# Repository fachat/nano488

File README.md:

# nano488

An IEEE488 interface for the PC using USB and an Arduino Nano (tm)

## Design

This IEEE488 interfaces uses an Arduino Nano (tm) and its serial-over-USB interface to have a PC control the IEEE488 interface.

The design is made to be able to work as both, a controller or a device, but the main purpose is to work as
a disk drive for the Commodore PET computers.

The design is inspired by https://github.com/Twilight-Logic/AR488 but I had to rearrange some lines to
add the Commodore disk drive's ATNA response circuit.

Also, the design uses the standards compliant 75160/75161 IEEE488 drivers, so electrical specifications are met.

Note, that no extra power supply line e.g. to the tape port is required, as the board is using the 5V
supplied by the USB bus connector (via the Arduino nano (tm))

## Software

The software that supports the disk drive functionality is XD2031 ( https://github.com/fachat/XD2031 ) - for details see there.

## Boards

### V1.1B

This board has four IEEE488 connectors:

1. a board edge connector similar to the Commodore PET IEEE488 connector
2. a slot connector to plug the device directly onto the Commodore PET IEEE488 connector
3. a 24 pin standards IEEE488 connector for standard IEEE488 stacking cables
4. a 24 pin flat ribbon connector

Here are the design files:

- [Eagle schematics](v1.1b/nano_ieee488_v1.1b.sch)
- [Eagle layout](v1.1b/nano_ieee488_v1.1b.brd)
- [Schematics picture](v1.1b/nano_ieee488_v1.1b-sch.png)
- [Board parts layout](v1.1b/nano_ieee488_v1.1b-layout.png)
- [Board full layout](v1.1b/nano_ieee488_v1.1b-brd.png)
- [Gerber files](v1.1b/nano_ieee488_v1.1b-gerbers.zip)

### V1.0B

This board has four IEEE488 connectors:

1. a board edge connector similar to the Commodore PET IEEE488 connector
1. a 24 pin standards IEEE488 connector for standard IEEE488 stacking cables
1. a 24 pin flat ribbon connector

Here are the design files:

- [Eagle schematics](v1.0b/nano_ieee488_v1.0b.sch)
- [Eagle layout](v1.0b/nano_ieee488_v1.0b.brd)
- [Schematics picture](v1.0b/nano_ieee488_v1.0b-sch.png)
- [Board parts layout](v1.0b/nano_ieee488_v1.0b-layout.png)
- [Board full layout](v1.0b/nano_ieee488_v1.0b-brd.png)

## Gallery

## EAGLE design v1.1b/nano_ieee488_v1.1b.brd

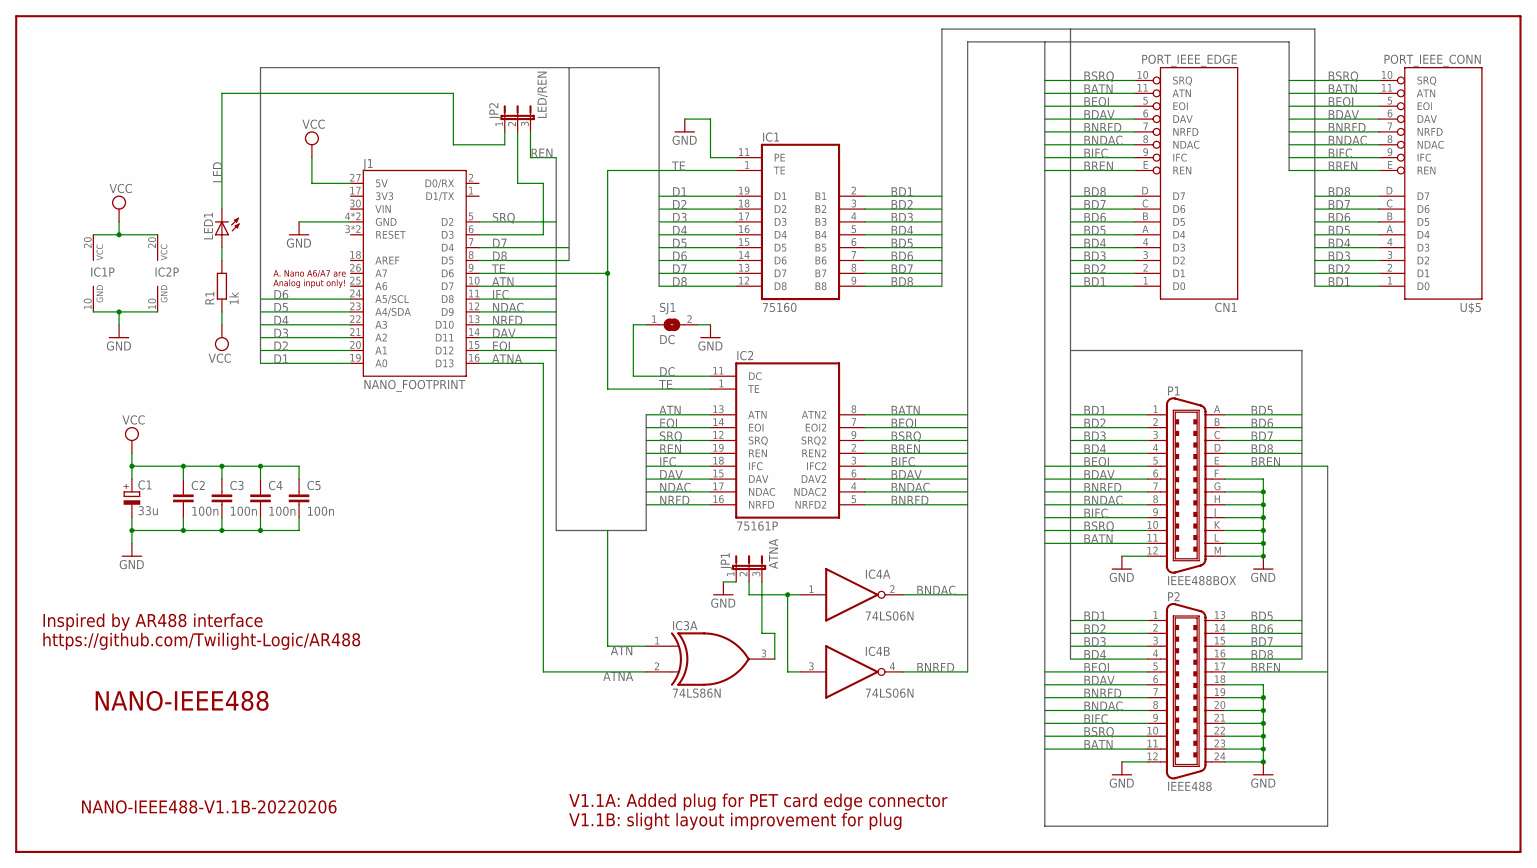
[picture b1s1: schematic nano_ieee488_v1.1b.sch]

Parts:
C1: 33u; E2,5-7
C2, C3, C4, C5: 100n; C025-025X050
CN1: PORT_IEEE_EDGE; MA156_12-2_IEEE
IC1: 75160; DIL20
IC2: 75161P; DIL20
IC3: 74LS86N; DIL14
IC4: 74LS06N; DIL14
J1: NANO_FOOTPRINT; NANO
JP1: ATNA; JP2
JP2: LED/REN; JP2
LED1: LED3MM
P1: IEEE488BOX; FLAT24BOX
P2: IEEE488; 24HP
R1: 1k; 0204/5
SJ1: DC; SJW
U$5: PORT_IEEE_CONN; MA156_12-2_SHORT

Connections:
ATN: IC2.13 (ATN), IC3.1 (I0), J1.10 (D7)
ATNA: IC3.2 (I1), J1.16 (D13)
BATN: CN1.11 (ATN), IC2.8 (ATN2), P1.11, P2.11, U$5.11 (ATN)
BD1: CN1.1 (D0), IC1.2 (B1), P1.1, P2.1, U$5.1 (D0)
BD2: CN1.2 (D1), IC1.3 (B2), P1.2, P2.2, U$5.2 (D1)
BD3: CN1.3 (D2), IC1.4 (B3), P1.3, P2.3, U$5.3 (D2)
BD4: CN1.4 (D3), IC1.5 (B4), P1.4, P2.4, U$5.4 (D3)
BD5: CN1.A (D4), IC1.6 (B5), P1.A (13), P2.13, U$5.A (D4)
BD6: CN1.B (D5), IC1.7 (B6), P1.B (14), P2.14, U$5.B (D5)
BD7: CN1.C (D6), IC1.8 (B7), P1.C (15), P2.15, U$5.C (D6)
BD8: CN1.D (D7), IC1.9 (B8), P1.D (16), P2.16, U$5.D (D7)
BDAV: CN1.6 (DAV), IC2.6 (DAV2), P1.6, P2.6, U$5.6 (DAV)
BEOI: CN1.5 (EOI), IC2.7 (EOI2), P1.5, P2.5, U$5.5 (EOI)
BIFC: CN1.9 (IFC), IC2.3 (IFC2), P1.9, P2.9, U$5.9 (IFC)
BNDAC: CN1.8 (NDAC), IC2.4 (NDAC2), IC4.2 (O), P1.8, P2.8, U$5.8 (NDAC)
BNRFD: CN1.7 (NRFD), IC2.5 (NRFD2), IC4.4 (O), P1.7, P2.7, U$5.7 (NRFD)
BREN: CN1.E (REN), IC2.2 (REN2), P1.E (17), P2.17, U$5.E (REN)
BSRQ: CN1.10 (SRQ), IC2.9 (SRQ2), P1.10, P2.10, U$5.10 (SRQ)
D1: IC1.19 (D1), J1.19 (A0)
D2: IC1.18 (D2), J1.20 (A1)
D3: IC1.17 (D3), J1.21 (A2)
D4: IC1.16 (D4), J1.22 (A3)
D5: IC1.15 (D5), J1.23 (A4/SDA)
D6: IC1.14 (D6), J1.24 (A5/SCL)
D7: IC1.13 (D7), J1.7 (D4)
D8: IC1.12 (D8), J1.8 (D5)
DAV: IC2.15 (DAV), J1.14 (D11)
DC: IC2.11 (DC), SJ1.1
EOI: IC2.14 (EOI), J1.15 (D12)
GND: C1.-, C2.2, C3.2, C4.2, C5.2, CN1.12 (GND), CN1.F (GND), CN1.H (GND), CN1.J (GND), CN1.K (GND), CN1.L (GND), CN1.M (GND), CN1.N (GND), IC1.10 (GND), IC1.11 (PE), IC2.10 (GND), IC3.7 (GND), IC4.7 (GND), J1.4 (GND), J1.29 (GND), JP1.1, P1.12, P1.F (18), P1.G (19), P1.H (20), P1.J (21), P1.K (22), P1.L (23), P1.M (24), P2.12, P2.18, P2.19, P2.20, P2.21, P2.22, P2.23, P2.24, SJ1.2, U$5.12 (GND), U$5.F (GND), U$5.H (GND), U$5.J (GND), U$5.K (GND), U$5.L (GND), U$5.M (GND), U$5.N (GND)
IFC: IC2.18 (IFC), J1.11 (D8)
LED: JP2.1, LED1.K (C)
unnamed: IC3.3 (O), JP1.3
unnamed: IC4.1 (I), IC4.3 (I), JP1.2
unnamed: LED1.A, R1.2
unnamed: J1.6 (D3), JP2.2
NDAC: IC2.17 (NDAC), J1.12 (D9)
NRFD: IC2.16 (NRFD), J1.13 (D10)
REN: IC2.19 (REN), JP2.3
SRQ: IC2.12 (SRQ), J1.5 (D2)
TE: IC1.1 (TE), IC2.1 (TE), J1.9 (D6)
VCC: C1.+, C2.1, C3.1, C4.1, C5.1, IC1.20 (VCC), IC2.20 (VCC), IC3.14 (VCC), IC4.14 (VCC), J1.27 (5V), R1.1

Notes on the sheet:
NANO-IEEE488
NANO-IEEE488-V1.1B-20220206
Inspired by AR488 interface https://github.com/Twilight-Logic/AR488
A. Nano A6/A7 are Analog input only!
V1.1A: Added plug for PET card edge connector V1.1B: slight layout improvement for plug

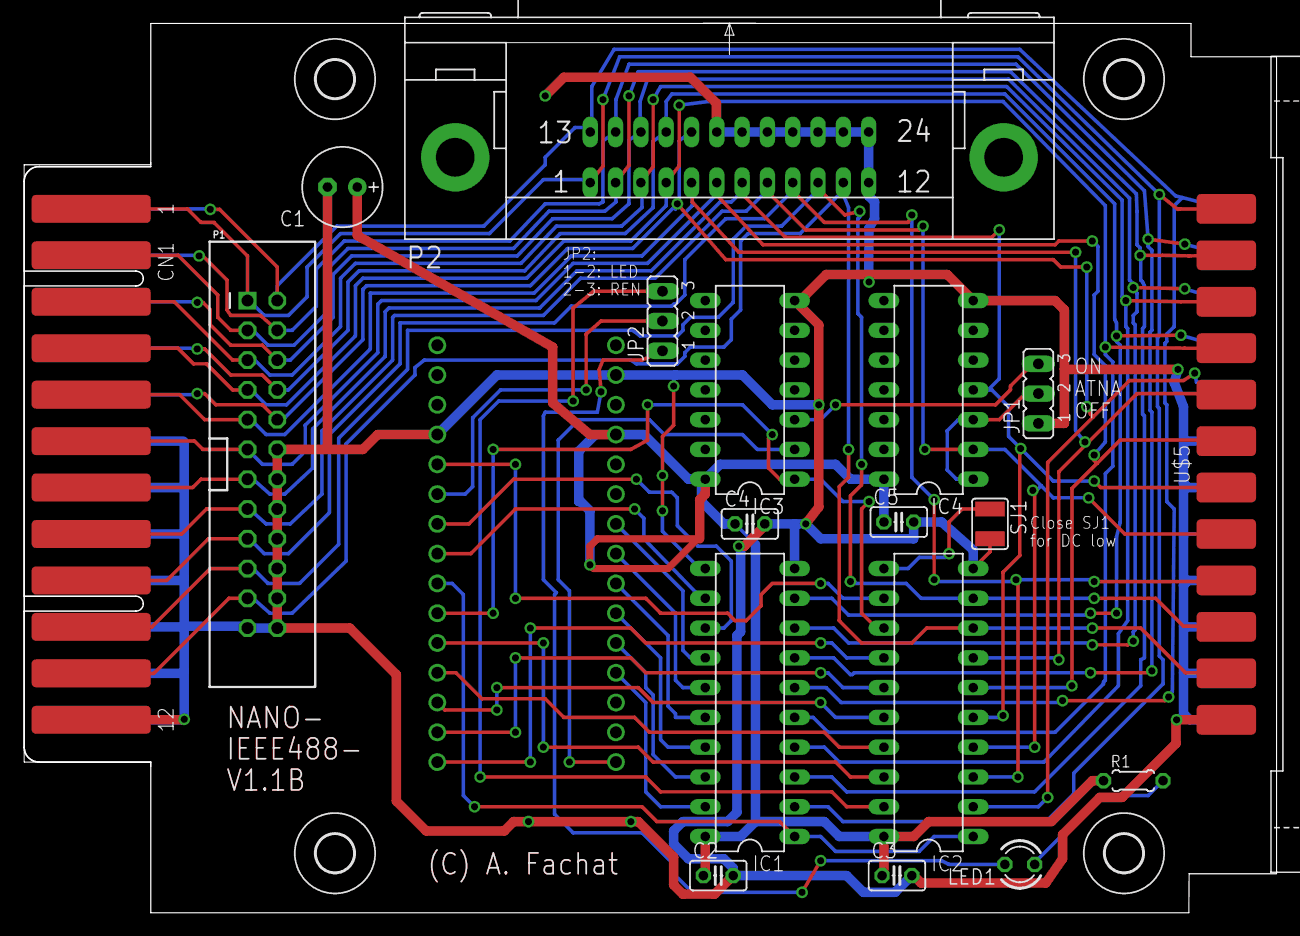
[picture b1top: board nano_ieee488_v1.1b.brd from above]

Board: 2 copper layers, 106.8 x 75.7 mm, 23 parts (0 on the bottom side), 42 nets.

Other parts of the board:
U$1, U$2, U$3, U$4: 3,2

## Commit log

2022-02-06 initial commit, with v1.0b and v1.1b
2022-02-06 fix layout links
2022-02-07 add gerbers

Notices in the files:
parts and their libraries:
SparkFun-Boards: Licensing: Creative Commons ShareAlike 4.0 International - https://creativecommons.org/licenses/by-sa/4.0
